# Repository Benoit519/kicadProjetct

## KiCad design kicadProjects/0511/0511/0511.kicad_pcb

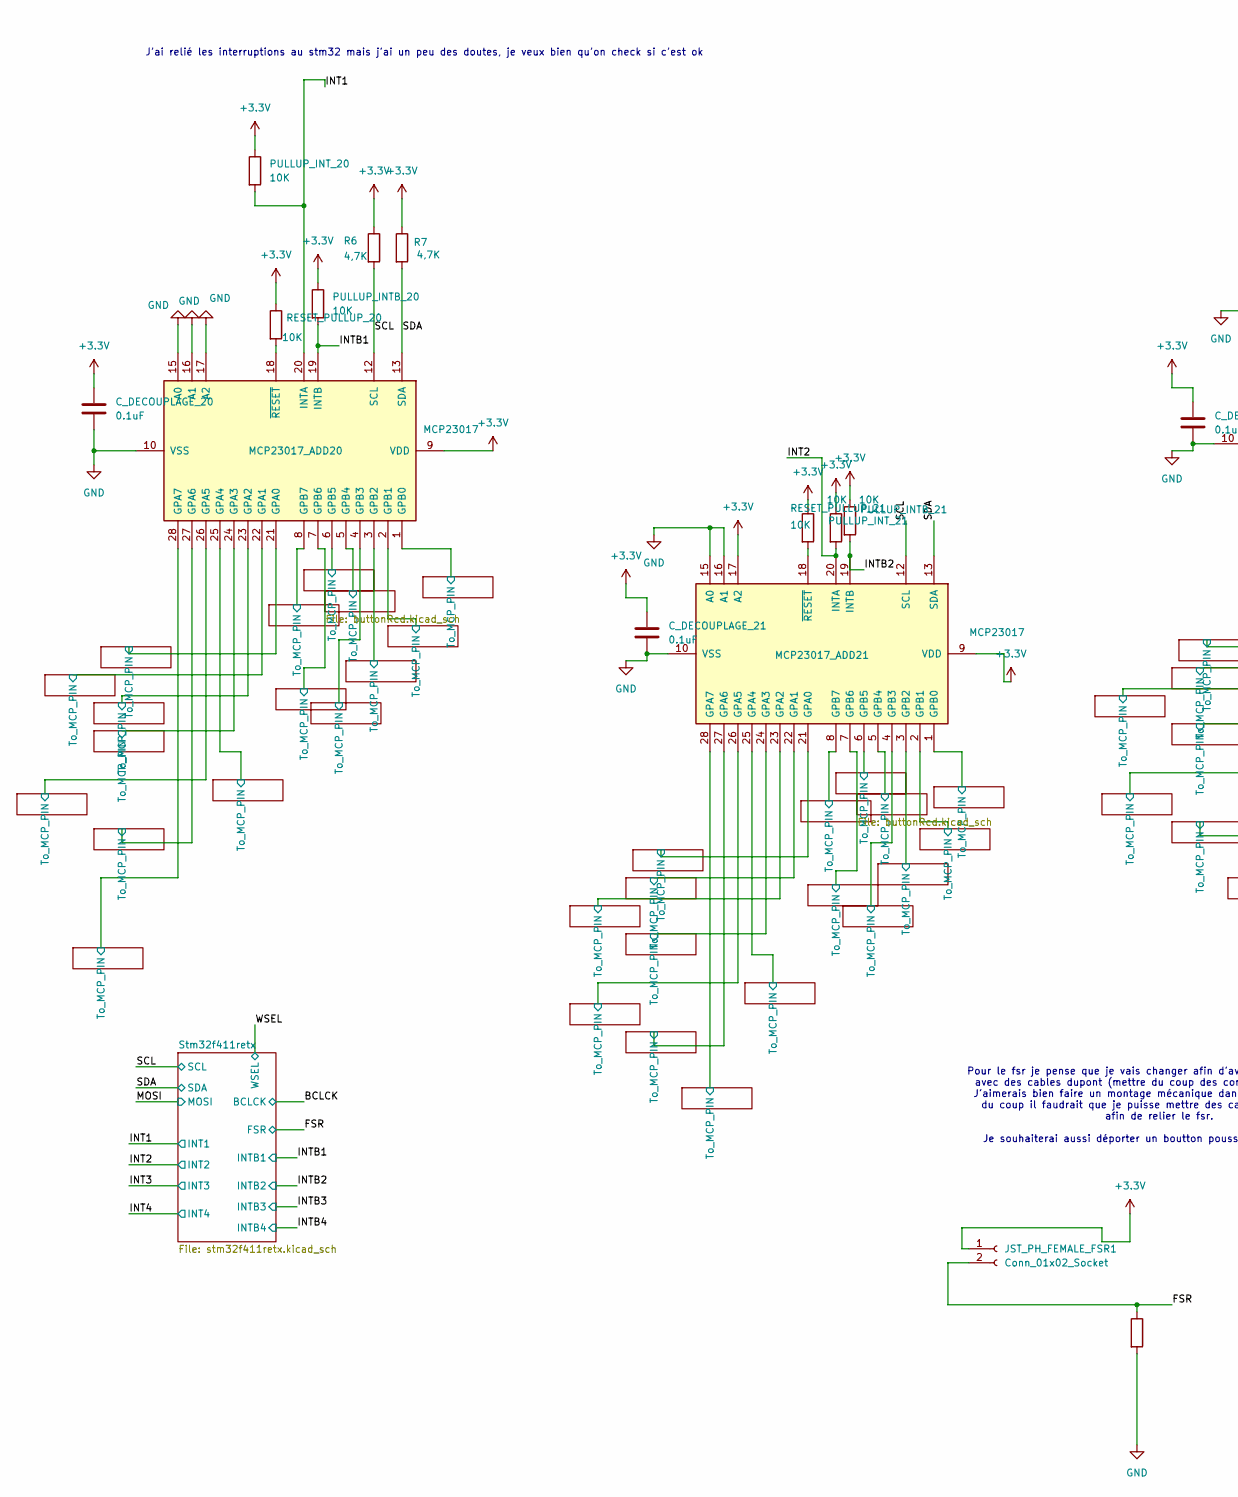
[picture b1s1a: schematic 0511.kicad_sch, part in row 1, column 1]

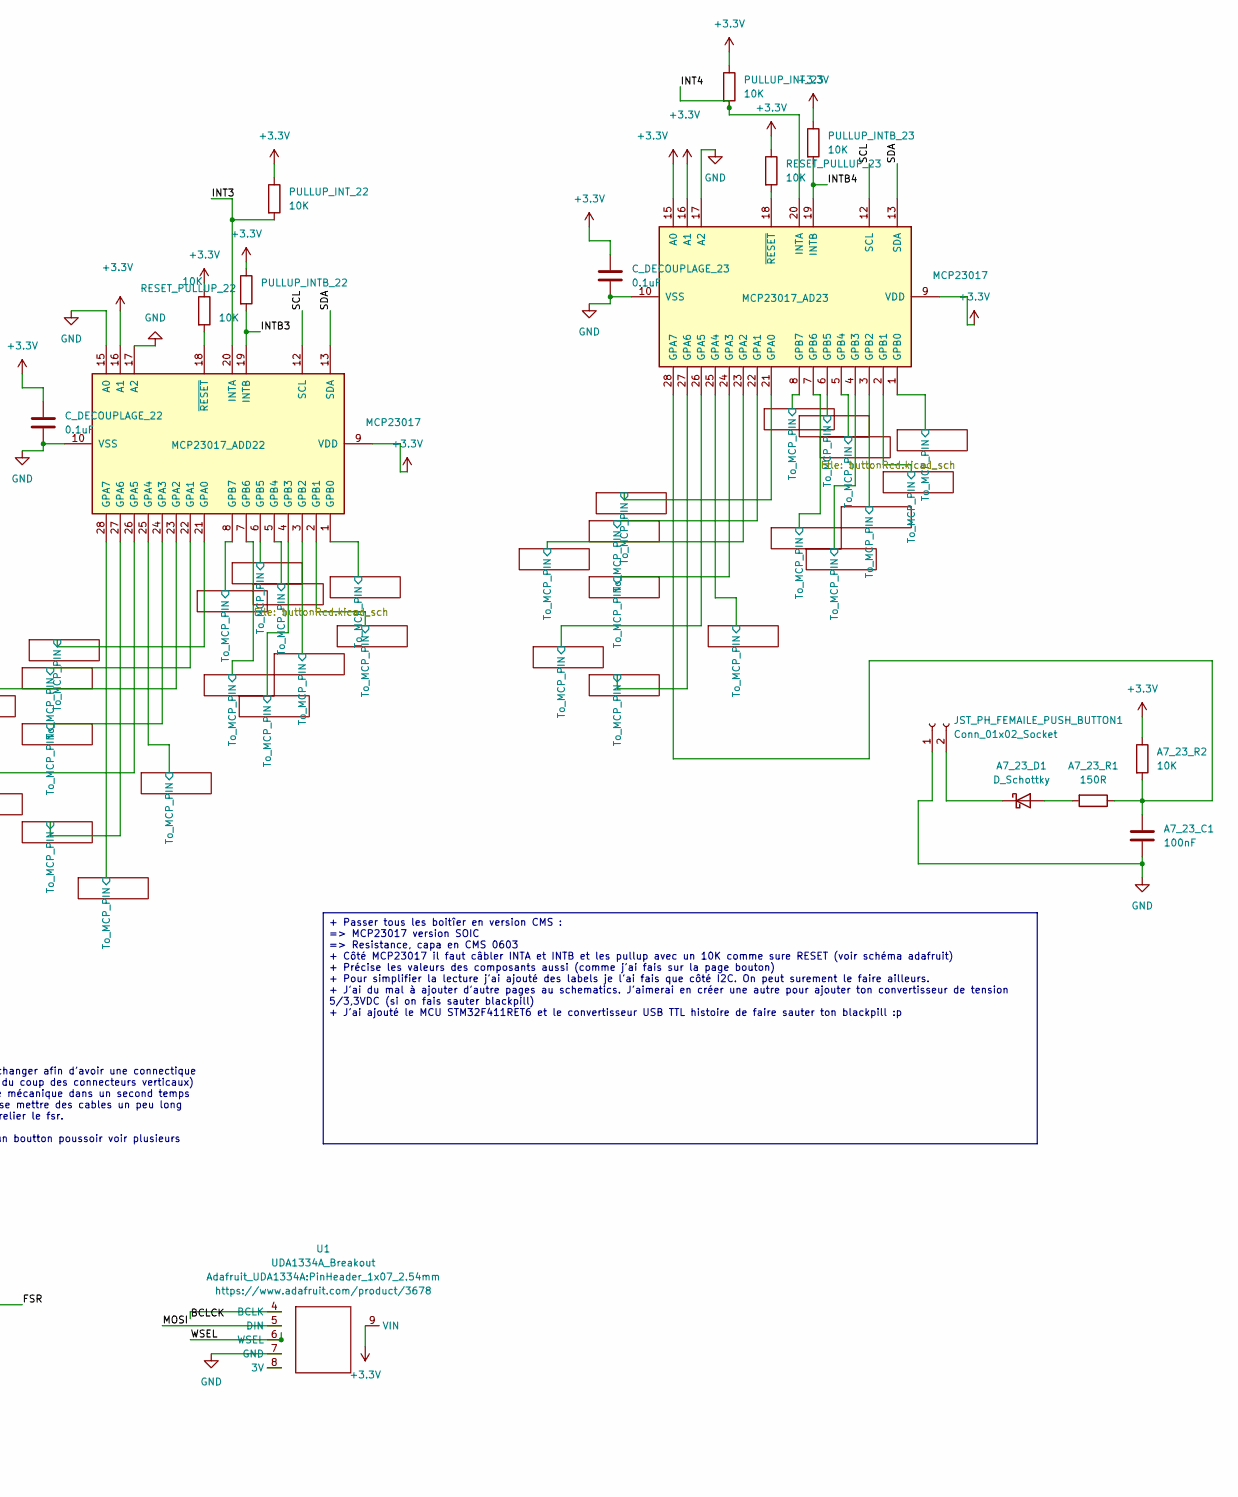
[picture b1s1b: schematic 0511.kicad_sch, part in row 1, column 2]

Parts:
A7_23_C1: 100nF; C_0603_1608Metric
A7_23_D1: D_Schottky; D_SOD-123
A7_23_R1: 150R; R_0603_1608Metric
A7_23_R2: 10K; R_0603_1608Metric
C_DECOUPLAGE_20, C_DECOUPLAGE_21, C_DECOUPLAGE_22, C_DECOUPLAGE_23: 0.1uF; C_0603_1608Metric
JST_PH_FEMAILE_PUSH_BUTTON1: Conn_01x02_Socket; JST_PH_B2B-PH-SM4-TB_1x02-1MP_P2.00mm_Vertical
JST_PH_FEMALE_FSR1: Conn_01x02_Socket; JST_PH_B2B-PH-SM4-TB_1x02-1MP_P2.00mm_Vertical
MCP23017_AD23, MCP23017_ADD20, MCP23017_ADD21, MCP23017_ADD22: MCP23017; SOIC-28W_7.5x17.9mm_P1.27mm
PULLUP_INTB_20, PULLUP_INTB_21, PULLUP_INTB_22, PULLUP_INTB_23: 10K; R_0603_1608Metric
PULLUP_INT_20, PULLUP_INT_21, PULLUP_INT_22, PULLUP_INT_23: 10K; R_0603_1608Metric
R6, R7: 4,7K; R_0603_1608Metric
R17: 22K; R_0603_1608Metric
RESET_PULLUP_20, RESET_PULLUP_21, RESET_PULLUP_22, RESET_PULLUP_23: 10K; R_0603_1608Metric
U1: UDA1334A_Breakout; PinHeader_1x07_2.54mm

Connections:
+3.3V: A7_23_R2.1, C_DECOUPLAGE_20.1, C_DECOUPLAGE_21.1, C_DECOUPLAGE_22.1, C_DECOUPLAGE_23.1, JST_PH_FEMALE_FSR1.1, MCP23017_AD23.9 (VDD), MCP23017_AD23.15 (A0), MCP23017_AD23.16 (A1), MCP23017_ADD20.9 (VDD), MCP23017_ADD21.9 (VDD), MCP23017_ADD21.17 (A2), MCP23017_ADD22.9 (VDD), MCP23017_ADD22.16 (A1), PULLUP_INTB_20.1, PULLUP_INTB_21.1, PULLUP_INTB_22.1, PULLUP_INTB_23.1, PULLUP_INT_20.1, PULLUP_INT_21.1, PULLUP_INT_22.1, PULLUP_INT_23.1, R6.1, R7.1, RESET_PULLUP_20.1, RESET_PULLUP_21.1, RESET_PULLUP_22.1, RESET_PULLUP_23.1, U1.9 (VIN); also elsewhere on the board
/BCLCK: U1.4 (BCLK); also elsewhere on the board
/Button_RCD16/To_MCP_PIN: MCP23017_ADD21.27 (GPA6); also elsewhere on the board
/Button_RCD17/To_MCP_PIN: MCP23017_ADD21.26 (GPA5); also elsewhere on the board
/Button_RCD19/To_MCP_PIN: MCP23017_ADD20.27 (GPA6); also elsewhere on the board
/Button_RCD20/To_MCP_PIN: MCP23017_ADD21.23 (GPA2); also elsewhere on the board
/Button_RCD21/To_MCP_PIN: MCP23017_ADD21.22 (GPA1); also elsewhere on the board
/Button_RCD22/To_MCP_PIN: MCP23017_ADD21.21 (GPA0); also elsewhere on the board
/Button_RCD23/To_MCP_PIN: MCP23017_ADD21.8 (GPB7); also elsewhere on the board
/Button_RCD24/To_MCP_PIN: MCP23017_ADD21.6 (GPB5); also elsewhere on the board
/Button_RCD25/To_MCP_PIN: MCP23017_ADD21.5 (GPB4); also elsewhere on the board
/Button_RCD26/To_MCP_PIN: MCP23017_ADD21.4 (GPB3); also elsewhere on the board
/Button_RCD27/To_MCP_PIN: MCP23017_ADD21.3 (GPB2); also elsewhere on the board
/Button_RCD28/To_MCP_PIN: MCP23017_ADD21.2 (GPB1); also elsewhere on the board
/Button_RCD29/To_MCP_PIN: MCP23017_ADD21.1 (GPB0); also elsewhere on the board
/Button_RCD30/To_MCP_PIN: MCP23017_ADD21.28 (GPA7); also elsewhere on the board
/Button_RCD31/To_MCP_PIN: MCP23017_ADD21.7 (GPB6); also elsewhere on the board
/Button_RCD32/To_MCP_PIN: MCP23017_ADD22.27 (GPA6); also elsewhere on the board
/Button_RCD33/To_MCP_PIN: MCP23017_ADD22.26 (GPA5); also elsewhere on the board
/Button_RCD35/To_MCP_PIN: MCP23017_ADD22.23 (GPA2); also elsewhere on the board
/Button_RCD36/To_MCP_PIN: MCP23017_ADD22.22 (GPA1); also elsewhere on the board
/Button_RCD37/To_MCP_PIN: MCP23017_ADD22.21 (GPA0); also elsewhere on the board
/Button_RCD38/To_MCP_PIN: MCP23017_ADD22.28 (GPA7); also elsewhere on the board
/Button_RCD39/To_MCP_PIN: MCP23017_ADD22.8 (GPB7); also elsewhere on the board
/Button_RCD40/To_MCP_PIN: MCP23017_ADD22.6 (GPB5); also elsewhere on the board
/Button_RCD41/To_MCP_PIN: MCP23017_ADD22.5 (GPB4); also elsewhere on the board
/Button_RCD42/To_MCP_PIN: MCP23017_ADD22.4 (GPB3); also elsewhere on the board
/Button_RCD43/To_MCP_PIN: MCP23017_ADD22.3 (GPB2); also elsewhere on the board
/Button_RCD44/To_MCP_PIN: MCP23017_ADD22.2 (GPB1); also elsewhere on the board
/Button_RCD45/To_MCP_PIN: MCP23017_ADD22.1 (GPB0); also elsewhere on the board
/Button_RCD46/To_MCP_PIN: MCP23017_AD23.27 (GPA6); also elsewhere on the board
/Button_RCD47/To_MCP_PIN: MCP23017_ADD22.7 (GPB6); also elsewhere on the board
/Button_RCD48/To_MCP_PIN: MCP23017_AD23.26 (GPA5); also elsewhere on the board
/Button_RCD50/To_MCP_PIN: MCP23017_AD23.23 (GPA2); also elsewhere on the board
/Button_RCD51/To_MCP_PIN: MCP23017_AD23.22 (GPA1); also elsewhere on the board
/Button_RCD52/To_MCP_PIN: MCP23017_AD23.21 (GPA0); also elsewhere on the board
/Button_RCD56/To_MCP_PIN: MCP23017_AD23.6 (GPB5); also elsewhere on the board
/Button_RCD57/To_MCP_PIN: MCP23017_AD23.5 (GPB4); also elsewhere on the board
/Button_RCD58/To_MCP_PIN: MCP23017_AD23.4 (GPB3); also elsewhere on the board
/Button_RCD59/To_MCP_PIN: MCP23017_AD23.3 (GPB2); also elsewhere on the board
/Button_RCD60/To_MCP_PIN: MCP23017_AD23.2 (GPB1); also elsewhere on the board
/Button_RCD61/To_MCP_PIN: MCP23017_AD23.1 (GPB0); also elsewhere on the board
/Button_RCD62/To_MCP_PIN: MCP23017_AD23.8 (GPB7); also elsewhere on the board
/Button_RCD63/To_MCP_PIN: MCP23017_AD23.7 (GPB6); also elsewhere on the board
/Button_RCD64/To_MCP_PIN: MCP23017_ADD20.6 (GPB5); also elsewhere on the board
/Button_RCD65/To_MCP_PIN: MCP23017_ADD20.5 (GPB4); also elsewhere on the board
/Button_RCD66/To_MCP_PIN: MCP23017_ADD20.4 (GPB3); also elsewhere on the board
/Button_RCD67/To_MCP_PIN: MCP23017_ADD20.3 (GPB2); also elsewhere on the board
/Button_RCD68/To_MCP_PIN: MCP23017_ADD20.2 (GPB1); also elsewhere on the board
/Button_RCD69/To_MCP_PIN: MCP23017_ADD20.1 (GPB0); also elsewhere on the board
/Button_RCD70/To_MCP_PIN: MCP23017_ADD20.8 (GPB7); also elsewhere on the board
/Button_RCD71/To_MCP_PIN: MCP23017_ADD20.26 (GPA5); also elsewhere on the board
/Button_RCD73/To_MCP_PIN: MCP23017_ADD20.23 (GPA2); also elsewhere on the board
/Button_RCD74/To_MCP_PIN: MCP23017_ADD20.22 (GPA1); also elsewhere on the board
/Button_RCD75/To_MCP_PIN: MCP23017_ADD20.21 (GPA0); also elsewhere on the board
/Button_RCD76/To_MCP_PIN: MCP23017_ADD20.28 (GPA7); also elsewhere on the board
/Button_RCD77/To_MCP_PIN: MCP23017_ADD20.7 (GPB6); also elsewhere on the board
/Button_RCD79/To_MCP_PIN: MCP23017_ADD21.24 (GPA3); also elsewhere on the board
/Button_RCD80/To_MCP_PIN: MCP23017_ADD21.25 (GPA4); also elsewhere on the board
/Button_RCD81/To_MCP_PIN: MCP23017_ADD20.24 (GPA3); also elsewhere on the board
/Button_RCD82/To_MCP_PIN: MCP23017_ADD20.25 (GPA4); also elsewhere on the board
/Button_RCD83/To_MCP_PIN: MCP23017_ADD22.24 (GPA3); also elsewhere on the board
/Button_RCD84/To_MCP_PIN: MCP23017_ADD22.25 (GPA4); also elsewhere on the board
/Button_RCD85/To_MCP_PIN: MCP23017_AD23.24 (GPA3); also elsewhere on the board
/Button_RCD86/To_MCP_PIN: MCP23017_AD23.25 (GPA4); also elsewhere on the board
/FSR: JST_PH_FEMALE_FSR1.2, R17.1; also elsewhere on the board
/INT1: MCP23017_ADD20.20 (INTA), PULLUP_INT_20.2; also elsewhere on the board
/INT2: MCP23017_ADD21.20 (INTA), PULLUP_INT_21.2; also elsewhere on the board
/INT3: MCP23017_ADD22.20 (INTA), PULLUP_INT_22.2; also elsewhere on the board
/INT4: MCP23017_AD23.20 (INTA), PULLUP_INT_23.2; also elsewhere on the board
/INTB1: MCP23017_ADD20.19 (INTB), PULLUP_INTB_20.2; also elsewhere on the board
/INTB2: MCP23017_ADD21.19 (INTB), PULLUP_INTB_21.2; also elsewhere on the board
/INTB3: MCP23017_ADD22.19 (INTB), PULLUP_INTB_22.2; also elsewhere on the board
/INTB4: MCP23017_AD23.19 (INTB), PULLUP_INTB_23.2; also elsewhere on the board
/MOSI: U1.5 (DIN); also elsewhere on the board
/SCL: MCP23017_AD23.12 (SCL), MCP23017_ADD20.12 (SCL), MCP23017_ADD21.12 (SCL), MCP23017_ADD22.12 (SCL), R6.2; also elsewhere on the board
/SDA: MCP23017_AD23.13 (SDA), MCP23017_ADD20.13 (SDA), MCP23017_ADD21.13 (SDA), MCP23017_ADD22.13 (SDA), R7.2; also elsewhere on the board
/WSEL: U1.6 (WSEL); also elsewhere on the board
GND: A7_23_C1.2, C_DECOUPLAGE_20.2, C_DECOUPLAGE_21.2, C_DECOUPLAGE_22.2, C_DECOUPLAGE_23.2, JST_PH_FEMAILE_PUSH_BUTTON1.1, MCP23017_AD23.10 (VSS), MCP23017_AD23.17 (A2), MCP23017_ADD20.10 (VSS), MCP23017_ADD20.15 (A0), MCP23017_ADD20.16 (A1), MCP23017_ADD20.17 (A2), MCP23017_ADD21.10 (VSS), MCP23017_ADD21.15 (A0), MCP23017_ADD21.16 (A1), MCP23017_ADD22.10 (VSS), MCP23017_ADD22.15 (A0), MCP23017_ADD22.17 (A2), R17.2, U1.7 (GND); also elsewhere on the board
unnamed: A7_23_D1.2 (A), A7_23_R1.2
unnamed: A7_23_D1.1 (K), JST_PH_FEMAILE_PUSH_BUTTON1.2
unnamed: A7_23_C1.1, A7_23_R1.1, A7_23_R2.2, MCP23017_AD23.28 (GPA7)
unnamed: MCP23017_AD23.18 (~RESET), RESET_PULLUP_23.2
unnamed: MCP23017_ADD20.18 (~RESET), RESET_PULLUP_20.2
unnamed: MCP23017_ADD21.18 (~RESET), RESET_PULLUP_21.2
unnamed: MCP23017_ADD22.18 (~RESET), RESET_PULLUP_22.2

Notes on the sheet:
Pour le fsr je pense que je vais changer afin d'avoir une connectique avec des cables dupont (mettre du coup des connecteurs verticaux) J'aimerais bien faire un montage mécanique dans un second temps du coup il faudrait que je puisse mettre des cables un peu long afin de relier le fsr. Je souhaiter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
J'ai relié les interruptions au stm32 mais j'ai un peu des doutes, je veux bien qu'on check si c'est ok
+ Passer tous les boitîer en version CMS : => MCP23017 version SOIC => Resistance, capa en CMS 0603 + Côté MCP23017 il faut câbler INTA et INTB et les pullup avec un 10K comme sure RESET (voir schéma adafruit) + Précise les valeurs des composants aussi (comme j'ai fais sur la page bouton) + Pour si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

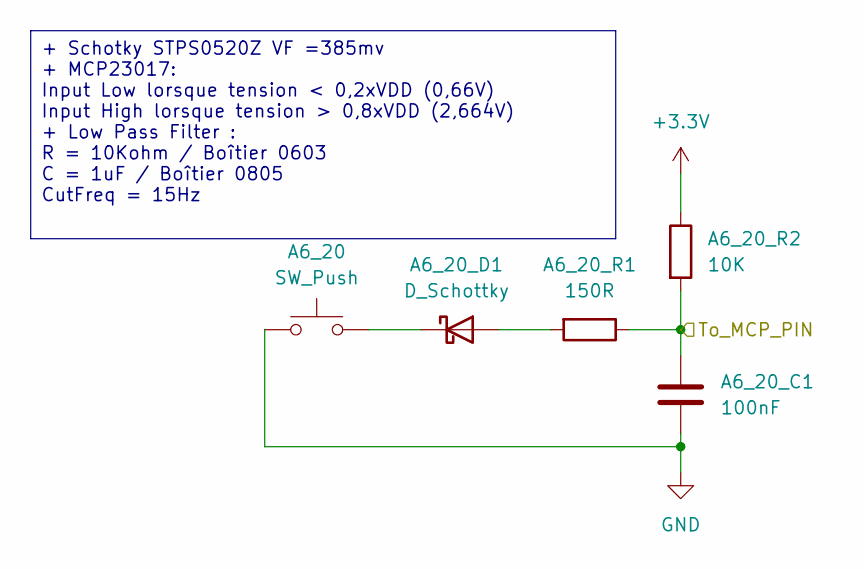
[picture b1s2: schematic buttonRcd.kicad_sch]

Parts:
A6_20: SW_Push; SW_Cherry_MX_1.00u_PCB
A6_20_C1: 100nF; C_0603_1608Metric
A6_20_D1: D_Schottky; D_SOD-123
A6_20_R1: 150R; R_0603_1608Metric
A6_20_R2: 10K; R_0603_1608Metric

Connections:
+3.3V: A6_20_R2.1; also elsewhere on the board
/Button_RCD19/To_MCP_PIN: A6_20_C1.1, A6_20_R1.1, A6_20_R2.2; also elsewhere on the board
GND: A6_20.1, A6_20_C1.2; also elsewhere on the board
unnamed: A6_20_D1.2 (A), A6_20_R1.2
unnamed: A6_20.2, A6_20_D1.1 (K)

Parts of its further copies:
A0_20, A0_21, A0_22, A0_23, A1_20, A1_21, A1_22, A1_23, A2_20, A2_21, A2_22, A2_23, A3_20, A3_21, A3_22, A3_23, A4_20, A4_21, A4_22, A4_23, A5_20, A5_21, A5_22, A5_23, A6_21, A6_22, A6_23, A7_20, A7_21, A7_22: SW_Push; SW_Cherry_MX_1.00u_PCB
A0_20_C1, A0_21_C1, A0_22_C1, A0_23_C1, A1_20_C1, A1_21_C1, A1_22_C1, A1_23_C1, A2_20_C1, A2_21_C1, A2_22_C1, A2_23_C1, A3_20_C1, A3_21_C1, A3_22_C1, A3_23_C1, A4_20_C1, A4_21_C1, A4_22_C1, A4_23_C1, A5_20_C1, A5_21_C1, A5_22_C1, A5_23_C1, A6_21_C1, A6_22_C1, A6_23_C1, A7_20_C1, A7_21_C1, A7_22_C1: 100nF; C_0603_1608Metric
A0_20_D1, A0_21_D1, A0_22_D1, A0_23_D1, A1_20_D1, A1_21_D1, A1_22_D1, A1_23_D1, A2_20_D1, A2_21_D1, A2_22_D1, A2_23_D1, A3_20_D1, A3_21_D1, A3_22_D1, A3_23_D1, A4_20_D1, A4_21_D1, A4_22_D1, A4_23_D1, A5_20_D1, A5_21_D1, A5_22_D1, A5_23_D1, A6_21_D1, A6_22_D1, A6_23_D1, A7_20_D1, A7_21_D1, A7_22_D1: D_Schottky; D_SOD-123
A0_20_R1, A0_21_R1, A0_22_R1, A0_23_R1, A1_20_R1, A1_21_R1, A1_22_R1, A1_23_R1, A2_20_R1, A2_21_R1, A2_22_R1, A2_23_R1, A3_20_R1, A3_21_R1, A3_22_R1, A3_23_R1, A4_20_R1, A4_21_R1, A4_22_R1, A4_23_R1, A5_20_R1, A5_21_R1, A5_22_R1, A5_23_R1, A6_21_R1, A6_22_R1, A6_23_R1, A7_20_R1, A7_21_R1, A7_22_R1: 150R; R_0603_1608Metric
A0_20_R2, A0_21_R2, A0_22_R2, A0_23_R2, A1_20_R2, A1_21_R2, A1_22_R2, A1_23_R2, A2_20_R2, A2_21_R2, A2_22_R2, A2_23_R2, A3_20_R2, A3_21_R2, A3_22_R2, A3_23_R2, A4_20_R2, A4_21_R2, A4_22_R2, A4_23_R2, A5_20_R2, A5_21_R2, A5_22_R2, A5_23_R2, A6_21_R2, A6_22_R2, A6_23_R2, A7_20_R2, A7_21_R2, A7_22_R2: 10K; R_0603_1608Metric
B0_20, B0_21, B0_22, B0_23, B1_20, B1_21, B1_22, B1_23, B2_20, B2_21, B2_22, B2_23, B3_20, B3_21, B3_22, B3_23, B4_20, B4_21, B4_22, B4_23, B5_20, B5_21, B5_22, B5_23, B6_20, B6_21, B6_22, B6_23, B7_20, B7_21, B7_22, B7_23: SW_Push; SW_Cherry_MX_1.00u_PCB
B0_20_C1, B0_21_C1, B0_22_C1, B0_23_C1, B1_20_C1, B1_21_C1, B1_22_C1, B1_23_C1, B2_20_C1, B2_21_C1, B2_22_C1, B2_23_C1, B3_20_C1, B3_21_C1, B3_22_C1, B3_23_C1, B4_20_C1, B4_21_C1, B4_22_C1, B4_23_C1, B5_20_C1, B5_21_C1, B5_22_C1, B5_23_C1, B6_20_C1, B6_21_C1, B6_22_C1, B6_23_C1, B7_20_C1, B7_21_C1, B7_22_C1, B7_23_C1: 100nF; C_0603_1608Metric
B0_20_D1, B0_21_D1, B0_22_D1, B0_23_D1, B1_20_D1, B1_21_D1, B1_22_D1, B1_23_D1, B2_20_D1, B2_21_D1, B2_22_D1, B2_23_D1, B3_20_D1, B3_21_D1, B3_22_D1, B3_23_D1, B4_20_D1, B4_21_D1, B4_22_D1, B4_23_D1, B5_20_D1, B5_21_D1, B5_22_D1, B5_23_D1, B6_20_D1, B6_21_D1, B6_22_D1, B6_23_D1, B7_20_D1, B7_21_D1, B7_22_D1, B7_23_D1: D_Schottky; D_SOD-123
B0_20_R1, B0_21_R1, B0_22_R1, B0_23_R1, B1_20_R1, B1_21_R1, B1_22_R1, B1_23_R1, B2_20_R1, B2_21_R1, B2_22_R1, B2_23_R1, B3_20_R1, B3_21_R1, B3_22_R1, B3_23_R1, B4_20_R1, B4_21_R1, B4_22_R1, B4_23_R1, B5_20_R1, B5_21_R1, B5_22_R1, B5_23_R1, B6_20_R1, B6_21_R1, B6_22_R1, B6_23_R1, B7_20_R1, B7_21_R1, B7_22_R1, B7_23_R1: 150R; R_0603_1608Metric
B0_20_R2, B0_21_R2, B0_22_R2, B0_23_R2, B1_20_R2, B1_21_R2, B1_22_R2, B1_23_R2, B2_20_R2, B2_21_R2, B2_22_R2, B2_23_R2, B3_20_R2, B3_21_R2, B3_22_R2, B3_23_R2, B4_20_R2, B4_21_R2, B4_22_R2, B4_23_R2, B5_20_R2, B5_21_R2, B5_22_R2, B5_23_R2, B6_20_R2, B6_21_R2, B6_22_R2, B6_23_R2, B7_20_R2, B7_21_R2, B7_22_R2, B7_23_R2: 10K; R_0603_1608Metric

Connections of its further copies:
+3.3V: A0_20_R2.1, A0_21_R2.1, A0_22_R2.1, A0_23_R2.1, A1_20_R2.1, A1_21_R2.1, A1_22_R2.1, A1_23_R2.1, A2_20_R2.1, A2_21_R2.1, A2_22_R2.1, A2_23_R2.1, A3_20_R2.1, A3_21_R2.1, A3_22_R2.1, A3_23_R2.1, A4_20_R2.1, A4_21_R2.1, A4_22_R2.1, A4_23_R2.1, A5_20_R2.1, A5_21_R2.1, A5_22_R2.1, A5_23_R2.1, A6_21_R2.1, A6_22_R2.1, A6_23_R2.1, A7_20_R2.1, A7_21_R2.1, A7_22_R2.1, B0_20_R2.1, B0_21_R2.1, B0_22_R2.1, B0_23_R2.1, B1_20_R2.1, B1_21_R2.1, B1_22_R2.1, B1_23_R2.1, B2_20_R2.1, B2_21_R2.1, B2_22_R2.1, B2_23_R2.1, B3_20_R2.1, B3_21_R2.1, B3_22_R2.1, B3_23_R2.1, B4_20_R2.1, B4_21_R2.1, B4_22_R2.1, B4_23_R2.1, B5_20_R2.1, B5_21_R2.1, B5_22_R2.1, B5_23_R2.1, B6_20_R2.1, B6_21_R2.1, B6_22_R2.1, B6_23_R2.1, B7_20_R2.1, B7_21_R2.1, B7_22_R2.1, B7_23_R2.1; also elsewhere on the board
/Button_RCD16/To_MCP_PIN: A6_21_C1.1, A6_21_R1.1, A6_21_R2.2; also elsewhere on the board
/Button_RCD17/To_MCP_PIN: A5_21_C1.1, A5_21_R1.1, A5_21_R2.2; also elsewhere on the board
/Button_RCD20/To_MCP_PIN: A2_21_C1.1, A2_21_R1.1, A2_21_R2.2; also elsewhere on the board
/Button_RCD21/To_MCP_PIN: A1_21_C1.1, A1_21_R1.1, A1_21_R2.2; also elsewhere on the board
/Button_RCD22/To_MCP_PIN: A0_21_C1.1, A0_21_R1.1, A0_21_R2.2; also elsewhere on the board
/Button_RCD23/To_MCP_PIN: B7_21_C1.1, B7_21_R1.1, B7_21_R2.2; also elsewhere on the board
/Button_RCD24/To_MCP_PIN: B5_21_C1.1, B5_21_R1.1, B5_21_R2.2; also elsewhere on the board
/Button_RCD25/To_MCP_PIN: B4_21_C1.1, B4_21_R1.1, B4_21_R2.2; also elsewhere on the board
/Button_RCD26/To_MCP_PIN: B3_21_C1.1, B3_21_R1.1, B3_21_R2.2; also elsewhere on the board
/Button_RCD27/To_MCP_PIN: B2_21_C1.1, B2_21_R1.1, B2_21_R2.2; also elsewhere on the board
/Button_RCD28/To_MCP_PIN: B1_21_C1.1, B1_21_R1.1, B1_21_R2.2; also elsewhere on the board
/Button_RCD29/To_MCP_PIN: B0_21_C1.1, B0_21_R1.1, B0_21_R2.2; also elsewhere on the board
/Button_RCD30/To_MCP_PIN: A7_21_C1.1, A7_21_R1.1, A7_21_R2.2; also elsewhere on the board
/Button_RCD31/To_MCP_PIN: B6_21_C1.1, B6_21_R1.1, B6_21_R2.2; also elsewhere on the board
/Button_RCD32/To_MCP_PIN: A6_22_C1.1, A6_22_R1.1, A6_22_R2.2; also elsewhere on the board
/Button_RCD33/To_MCP_PIN: A5_22_C1.1, A5_22_R1.1, A5_22_R2.2; also elsewhere on the board
/Button_RCD35/To_MCP_PIN: A2_22_C1.1, A2_22_R1.1, A2_22_R2.2; also elsewhere on the board
/Button_RCD36/To_MCP_PIN: A1_22_C1.1, A1_22_R1.1, A1_22_R2.2; also elsewhere on the board
/Button_RCD37/To_MCP_PIN: A0_22_C1.1, A0_22_R1.1, A0_22_R2.2; also elsewhere on the board
/Button_RCD38/To_MCP_PIN: A7_22_C1.1, A7_22_R1.1, A7_22_R2.2; also elsewhere on the board
/Button_RCD39/To_MCP_PIN: B7_22_C1.1, B7_22_R1.1, B7_22_R2.2; also elsewhere on the board
/Button_RCD40/To_MCP_PIN: B5_22_C1.1, B5_22_R1.1, B5_22_R2.2; also elsewhere on the board
/Button_RCD41/To_MCP_PIN: B4_22_C1.1, B4_22_R1.1, B4_22_R2.2; also elsewhere on the board
/Button_RCD42/To_MCP_PIN: B3_22_C1.1, B3_22_R1.1, B3_22_R2.2; also elsewhere on the board
/Button_RCD43/To_MCP_PIN: B2_22_C1.1, B2_22_R1.1, B2_22_R2.2; also elsewhere on the board
/Button_RCD44/To_MCP_PIN: B1_22_C1.1, B1_22_R1.1, B1_22_R2.2; also elsewhere on the board
/Button_RCD45/To_MCP_PIN: B0_22_C1.1, B0_22_R1.1, B0_22_R2.2; also elsewhere on the board
/Button_RCD46/To_MCP_PIN: A6_23_C1.1, A6_23_R1.1, A6_23_R2.2; also elsewhere on the board
/Button_RCD47/To_MCP_PIN: B6_22_C1.1, B6_22_R1.1, B6_22_R2.2; also elsewhere on the board
/Button_RCD48/To_MCP_PIN: A5_23_C1.1, A5_23_R1.1, A5_23_R2.2; also elsewhere on the board
/Button_RCD50/To_MCP_PIN: A2_23_C1.1, A2_23_R1.1, A2_23_R2.2; also elsewhere on the board
/Button_RCD51/To_MCP_PIN: A1_23_C1.1, A1_23_R1.1, A1_23_R2.2; also elsewhere on the board
/Button_RCD52/To_MCP_PIN: A0_23_C1.1, A0_23_R1.1, A0_23_R2.2; also elsewhere on the board
/Button_RCD56/To_MCP_PIN: B5_23_C1.1, B5_23_R1.1, B5_23_R2.2; also elsewhere on the board
/Button_RCD57/To_MCP_PIN: B4_23_C1.1, B4_23_R1.1, B4_23_R2.2; also elsewhere on the board
/Button_RCD58/To_MCP_PIN: B3_23_C1.1, B3_23_R1.1, B3_23_R2.2; also elsewhere on the board
/Button_RCD59/To_MCP_PIN: B2_23_C1.1, B2_23_R1.1, B2_23_R2.2; also elsewhere on the board
/Button_RCD60/To_MCP_PIN: B1_23_C1.1, B1_23_R1.1, B1_23_R2.2; also elsewhere on the board
/Button_RCD61/To_MCP_PIN: B0_23_C1.1, B0_23_R1.1, B0_23_R2.2; also elsewhere on the board
/Button_RCD62/To_MCP_PIN: B7_23_C1.1, B7_23_R1.1, B7_23_R2.2; also elsewhere on the board
/Button_RCD63/To_MCP_PIN: B6_23_C1.1, B6_23_R1.1, B6_23_R2.2; also elsewhere on the board
/Button_RCD64/To_MCP_PIN: B5_20_C1.1, B5_20_R1.1, B5_20_R2.2; also elsewhere on the board
/Button_RCD65/To_MCP_PIN: B4_20_C1.1, B4_20_R1.1, B4_20_R2.2; also elsewhere on the board
/Button_RCD66/To_MCP_PIN: B3_20_C1.1, B3_20_R1.1, B3_20_R2.2; also elsewhere on the board
/Button_RCD67/To_MCP_PIN: B2_20_C1.1, B2_20_R1.1, B2_20_R2.2; also elsewhere on the board
/Button_RCD68/To_MCP_PIN: B1_20_C1.1, B1_20_R1.1, B1_20_R2.2; also elsewhere on the board
/Button_RCD69/To_MCP_PIN: B0_20_C1.1, B0_20_R1.1, B0_20_R2.2; also elsewhere on the board
/Button_RCD70/To_MCP_PIN: B7_20_C1.1, B7_20_R1.1, B7_20_R2.2; also elsewhere on the board
/Button_RCD71/To_MCP_PIN: A5_20_C1.1, A5_20_R1.1, A5_20_R2.2; also elsewhere on the board
/Button_RCD73/To_MCP_PIN: A2_20_C1.1, A2_20_R1.1, A2_20_R2.2; also elsewhere on the board
/Button_RCD74/To_MCP_PIN: A1_20_C1.1, A1_20_R1.1, A1_20_R2.2; also elsewhere on the board
/Button_RCD75/To_MCP_PIN: A0_20_C1.1, A0_20_R1.1, A0_20_R2.2; also elsewhere on the board
/Button_RCD76/To_MCP_PIN: A7_20_C1.1, A7_20_R1.1, A7_20_R2.2; also elsewhere on the board
/Button_RCD77/To_MCP_PIN: B6_20_C1.1, B6_20_R1.1, B6_20_R2.2; also elsewhere on the board
/Button_RCD79/To_MCP_PIN: A3_21_C1.1, A3_21_R1.1, A3_21_R2.2; also elsewhere on the board
/Button_RCD80/To_MCP_PIN: A4_21_C1.1, A4_21_R1.1, A4_21_R2.2; also elsewhere on the board
/Button_RCD81/To_MCP_PIN: A3_20_C1.1, A3_20_R1.1, A3_20_R2.2; also elsewhere on the board
/Button_RCD82/To_MCP_PIN: A4_20_C1.1, A4_20_R1.1, A4_20_R2.2; also elsewhere on the board
/Button_RCD83/To_MCP_PIN: A3_22_C1.1, A3_22_R1.1, A3_22_R2.2; also elsewhere on the board
/Button_RCD84/To_MCP_PIN: A4_22_C1.1, A4_22_R1.1, A4_22_R2.2; also elsewhere on the board
/Button_RCD85/To_MCP_PIN: A3_23_C1.1, A3_23_R1.1, A3_23_R2.2; also elsewhere on the board
/Button_RCD86/To_MCP_PIN: A4_23_C1.1, A4_23_R1.1, A4_23_R2.2; also elsewhere on the board
GND: A0_20.1, A0_20_C1.2, A0_21.1, A0_21_C1.2, A0_22.1, A0_22_C1.2, A0_23.1, A0_23_C1.2, A1_20.1, A1_20_C1.2, A1_21.1, A1_21_C1.2, A1_22.1, A1_22_C1.2, A1_23.1, A1_23_C1.2, A2_20.1, A2_20_C1.2, A2_21.1, A2_21_C1.2, A2_22.1, A2_22_C1.2, A2_23.1, A2_23_C1.2, A3_20.1, A3_20_C1.2, A3_21.1, A3_21_C1.2, A3_22.1, A3_22_C1.2, A3_23.1, A3_23_C1.2, A4_20.1, A4_20_C1.2, A4_21.1, A4_21_C1.2, A4_22.1, A4_22_C1.2, A4_23.1, A4_23_C1.2, A5_20.1, A5_20_C1.2, A5_21.1, A5_21_C1.2, A5_22.1, A5_22_C1.2, A5_23.1, A5_23_C1.2, A6_21.1, A6_21_C1.2, A6_22.1, A6_22_C1.2, A6_23.1, A6_23_C1.2, A7_20.1, A7_20_C1.2, A7_21.1, A7_21_C1.2, A7_22.1, A7_22_C1.2, B0_20.1, B0_20_C1.2, B0_21.1, B0_21_C1.2, B0_22.1, B0_22_C1.2, B0_23.1, B0_23_C1.2, B1_20.1, B1_20_C1.2, B1_21.1, B1_21_C1.2, B1_22.1, B1_22_C1.2, B1_23.1, B1_23_C1.2, B2_20.1, B2_20_C1.2, B2_21.1, B2_21_C1.2, B2_22.1, B2_22_C1.2, B2_23.1, B2_23_C1.2, B3_20.1, B3_20_C1.2, B3_21.1, B3_21_C1.2, B3_22.1, B3_22_C1.2, B3_23.1, B3_23_C1.2, B4_20.1, B4_20_C1.2, B4_21.1, B4_21_C1.2, B4_22.1, B4_22_C1.2, B4_23.1, B4_23_C1.2, B5_20.1, B5_20_C1.2, B5_21.1, B5_21_C1.2, B5_22.1, B5_22_C1.2, B5_23.1, B5_23_C1.2, B6_20.1, B6_20_C1.2, B6_21.1, B6_21_C1.2, B6_22.1, B6_22_C1.2, B6_23.1, B6_23_C1.2, B7_20.1, B7_20_C1.2, B7_21.1, B7_21_C1.2, B7_22.1, B7_22_C1.2, B7_23.1, B7_23_C1.2; also elsewhere on the board
unnamed: A0_20_D1.2 (A), A0_20_R1.2
unnamed: A0_20.2, A0_20_D1.1 (K)
unnamed: A0_21_D1.2 (A), A0_21_R1.2
unnamed: A0_21.2, A0_21_D1.1 (K)
unnamed: A0_22_D1.2 (A), A0_22_R1.2
unnamed: A0_22.2, A0_22_D1.1 (K)
unnamed: A0_23_D1.2 (A), A0_23_R1.2
unnamed: A0_23.2, A0_23_D1.1 (K)
unnamed: A1_20_D1.2 (A), A1_20_R1.2
unnamed: A1_20.2, A1_20_D1.1 (K)
unnamed: A1_21_D1.2 (A), A1_21_R1.2
unnamed: A1_21.2, A1_21_D1.1 (K)
unnamed: A1_22_D1.2 (A), A1_22_R1.2
unnamed: A1_22.2, A1_22_D1.1 (K)
unnamed: A1_23_D1.2 (A), A1_23_R1.2
unnamed: A1_23.2, A1_23_D1.1 (K)
unnamed: A2_20_D1.2 (A), A2_20_R1.2
unnamed: A2_20.2, A2_20_D1.1 (K)
unnamed: A2_21_D1.2 (A), A2_21_R1.2
unnamed: A2_21.2, A2_21_D1.1 (K)
unnamed: A2_22_D1.2 (A), A2_22_R1.2
unnamed: A2_22.2, A2_22_D1.1 (K)
unnamed: A2_23_D1.2 (A), A2_23_R1.2
unnamed: A2_23.2, A2_23_D1.1 (K)
unnamed: A3_20_D1.2 (A), A3_20_R1.2
unnamed: A3_20.2, A3_20_D1.1 (K)
unnamed: A3_21_D1.2 (A), A3_21_R1.2
unnamed: A3_21.2, A3_21_D1.1 (K)
unnamed: A3_22_D1.2 (A), A3_22_R1.2
unnamed: A3_22.2, A3_22_D1.1 (K)
unnamed: A3_23_D1.2 (A), A3_23_R1.2
unnamed: A3_23.2, A3_23_D1.1 (K)
unnamed: A4_20_D1.2 (A), A4_20_R1.2
unnamed: A4_20.2, A4_20_D1.1 (K)
unnamed: A4_21_D1.2 (A), A4_21_R1.2
unnamed: A4_21.2, A4_21_D1.1 (K)
unnamed: A4_22_D1.2 (A), A4_22_R1.2
unnamed: A4_22.2, A4_22_D1.1 (K)
unnamed: A4_23_D1.2 (A), A4_23_R1.2
unnamed: A4_23.2, A4_23_D1.1 (K)
unnamed: A5_20_D1.2 (A), A5_20_R1.2
unnamed: A5_20.2, A5_20_D1.1 (K)
unnamed: A5_21_D1.2 (A), A5_21_R1.2
unnamed: A5_21.2, A5_21_D1.1 (K)
unnamed: A5_22_D1.2 (A), A5_22_R1.2
unnamed: A5_22.2, A5_22_D1.1 (K)
unnamed: A5_23_D1.2 (A), A5_23_R1.2
unnamed: A5_23.2, A5_23_D1.1 (K)
unnamed: A6_21_D1.2 (A), A6_21_R1.2
unnamed: A6_21.2, A6_21_D1.1 (K)
unnamed: A6_22_D1.2 (A), A6_22_R1.2
unnamed: A6_22.2, A6_22_D1.1 (K)
unnamed: A6_23_D1.2 (A), A6_23_R1.2
unnamed: A6_23.2, A6_23_D1.1 (K)
unnamed: A7_20_D1.2 (A), A7_20_R1.2
unnamed: A7_20.2, A7_20_D1.1 (K)
unnamed: A7_21_D1.2 (A), A7_21_R1.2
unnamed: A7_21.2, A7_21_D1.1 (K)
unnamed: A7_22_D1.2 (A), A7_22_R1.2
unnamed: A7_22.2, A7_22_D1.1 (K)
unnamed: B0_20_D1.2 (A), B0_20_R1.2
unnamed: B0_20.2, B0_20_D1.1 (K)
unnamed: B0_21_D1.2 (A), B0_21_R1.2
unnamed: B0_21.2, B0_21_D1.1 (K)
unnamed: B0_22_D1.2 (A), B0_22_R1.2
unnamed: B0_22.2, B0_22_D1.1 (K)
unnamed: B0_23_D1.2 (A), B0_23_R1.2
unnamed: B0_23.2, B0_23_D1.1 (K)
unnamed: B1_20_D1.2 (A), B1_20_R1.2
unnamed: B1_20.2, B1_20_D1.1 (K)
unnamed: B1_21_D1.2 (A), B1_21_R1.2
unnamed: B1_21.2, B1_21_D1.1 (K)
unnamed: B1_22_D1.2 (A), B1_22_R1.2
unnamed: B1_22.2, B1_22_D1.1 (K)
unnamed: B1_23_D1.2 (A), B1_23_R1.2
unnamed: B1_23.2, B1_23_D1.1 (K)
unnamed: B2_20_D1.2 (A), B2_20_R1.2
unnamed: B2_20.2, B2_20_D1.1 (K)
unnamed: B2_21_D1.2 (A), B2_21_R1.2
unnamed: B2_21.2, B2_21_D1.1 (K)
unnamed: B2_22_D1.2 (A), B2_22_R1.2
unnamed: B2_22.2, B2_22_D1.1 (K)
unnamed: B2_23_D1.2 (A), B2_23_R1.2
unnamed: B2_23.2, B2_23_D1.1 (K)
unnamed: B3_20_D1.2 (A), B3_20_R1.2
unnamed: B3_20.2, B3_20_D1.1 (K)
unnamed: B3_21_D1.2 (A), B3_21_R1.2
unnamed: B3_21.2, B3_21_D1.1 (K)
unnamed: B3_22_D1.2 (A), B3_22_R1.2
unnamed: B3_22.2, B3_22_D1.1 (K)
unnamed: B3_23_D1.2 (A), B3_23_R1.2
unnamed: B3_23.2, B3_23_D1.1 (K)
unnamed: B4_20_D1.2 (A), B4_20_R1.2
unnamed: B4_20.2, B4_20_D1.1 (K)
unnamed: B4_21_D1.2 (A), B4_21_R1.2
unnamed: B4_21.2, B4_21_D1.1 (K)
unnamed: B4_22_D1.2 (A), B4_22_R1.2
unnamed: B4_22.2, B4_22_D1.1 (K)
unnamed: B4_23_D1.2 (A), B4_23_R1.2
unnamed: B4_23.2, B4_23_D1.1 (K)
unnamed: B5_20_D1.2 (A), B5_20_R1.2
unnamed: B5_20.2, B5_20_D1.1 (K)
unnamed: B5_21_D1.2 (A), B5_21_R1.2
unnamed: B5_21.2, B5_21_D1.1 (K)
unnamed: B5_22_D1.2 (A), B5_22_R1.2
unnamed: B5_22.2, B5_22_D1.1 (K)
unnamed: B5_23_D1.2 (A), B5_23_R1.2
unnamed: B5_23.2, B5_23_D1.1 (K)
unnamed: B6_20_D1.2 (A), B6_20_R1.2
unnamed: B6_20.2, B6_20_D1.1 (K)
unnamed: B6_21_D1.2 (A), B6_21_R1.2
unnamed: B6_21.2, B6_21_D1.1 (K)
unnamed: B6_22_D1.2 (A), B6_22_R1.2
unnamed: B6_22.2, B6_22_D1.1 (K)
unnamed: B6_23_D1.2 (A), B6_23_R1.2
unnamed: B6_23.2, B6_23_D1.1 (K)
unnamed: B7_20_D1.2 (A), B7_20_R1.2
unnamed: B7_20.2, B7_20_D1.1 (K)
unnamed: B7_21_D1.2 (A), B7_21_R1.2
unnamed: B7_21.2, B7_21_D1.1 (K)
unnamed: B7_22_D1.2 (A), B7_22_R1.2
unnamed: B7_22.2, B7_22_D1.1 (K)
unnamed: B7_23_D1.2 (A), B7_23_R1.2
unnamed: B7_23.2, B7_23_D1.1 (K)

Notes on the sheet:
+ Schotky STPS0520Z VF =385mv + MCP23017: Input Low lorsque tension < 0,2xVDD (0,66V) Input High lorsque tension > 0,8xVDD (2,664V) + Low Pass Filter : R = 10Kohm / Boîtier 0603 C = 1uF / Boîtier 0805 CutFreq = 15Hz
